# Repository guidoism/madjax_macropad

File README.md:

# MadJax Macropad

## Parts

* 1x [Seeed Studio XIAO RP2040](https://www.seeedstudio.com/XIAO-RP2040-v1-0-p-5026.html)
* 17x [Through-hole diodes]()
* 16x [MX-style key switches]()
* 16x [MX-style key caps]()
* 4x [Silicone feet]()
* 1x [USB-C cable]()
* 1x [EC11 Rotary Encoder]()

## Instructions

1. Solder the 17 through-hole diodes onto the front of the PCB
2. Solder the microcontroller onto the front of the PCB
3. Solder the 16 switches
4. Solder the rotary encoder

## Cost on JLCPCB

* 5x $2 + $1.52 shipping
* 10x $5 + $8.11 shipping
* 15x $12.80 + $11.92 shipping
* 20x $15.70 + $14.15 shipping

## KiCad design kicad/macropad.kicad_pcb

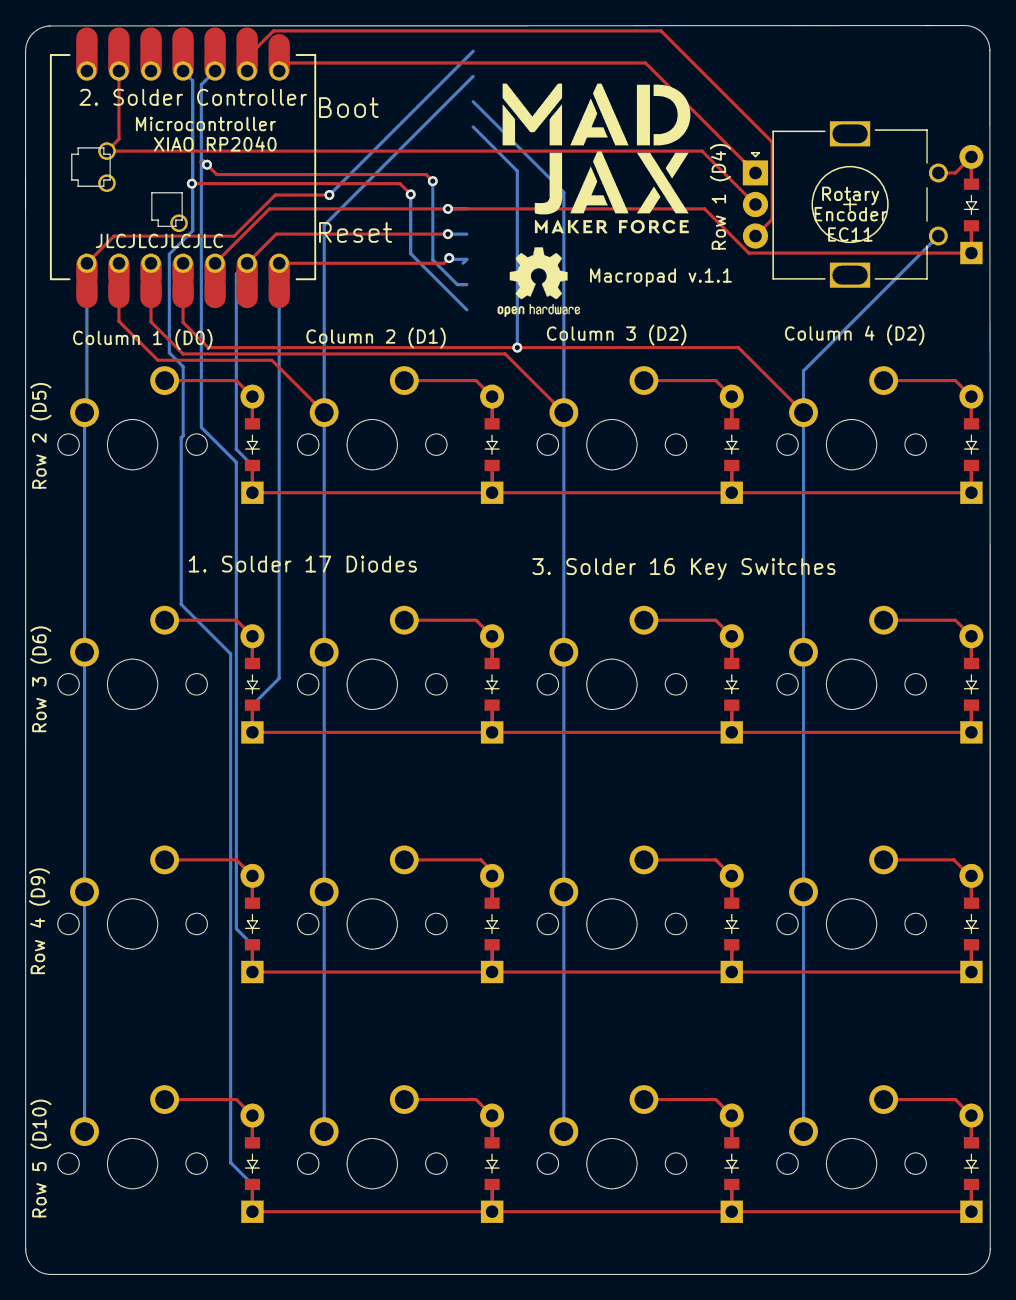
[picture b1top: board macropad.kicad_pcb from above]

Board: 2 copper layers, 76.4 x 99.0 mm, 35 parts (0 on the bottom side), 29 nets.

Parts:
D1, D2, D3, D4, D5, D6, D7, D8, D9, D10, D11, D12, D13, D14, D15, D16, D17: ComboDiode
ROT1: rotary_encoder
S1, S2, S3, S4, S5, S6, S7, S8, S9, S10, S11, S12, S13, S14, S15, S16: MX
_1: Seeeduino XIAO nRF52840

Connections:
ENCA: ROT1.A, _1.8
ENCB: ROT1.B, _1.9
GND: ROT1.C, _1.13
col1: S1.2, S2.2, S3.2, S4.2, _1.1
col1_row2: D4.2, S4.1
col1_row3: D3.2, S3.1
col1_row4: D2.2, S2.1
col1_row5: D1.2, S1.1
col2: S5.2, S6.2, S7.2, S8.2, _1.2
col2_row2: D8.2, S8.1
col2_row3: D7.2, S7.1
col2_row4: D6.2, S6.1
col2_row5: D5.2, S5.1
col3: S9.2, S10.2, S11.2, S12.2, _1.3
col3_row2: D12.2, S12.1
col3_row3: D11.2, S11.1
col3_row4: D10.2, S10.1
col3_row5: D9.2, S9.1
col4: ROT1.2, S13.2, S14.2, S15.2, S16.2, _1.4
col4_row1: D17.2, ROT1.1
col4_row2: D16.2, S16.1
col4_row3: D15.2, S15.1
col4_row4: D14.2, S14.1
col4_row5: D13.2, S13.1
row1: D17.1, _1.5
row2: D4.1, D8.1, D12.1, D16.1, _1.6
row3: D3.1, D7.1, D11.1, D15.1, _1.7
row4: D2.1, D6.1, D10.1, D14.1, _1.10
row5: D1.1, D5.1, D9.1, D13.1, _1.11

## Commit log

2024-10-25 added kicad design
2024-10-25 Checkpoint
